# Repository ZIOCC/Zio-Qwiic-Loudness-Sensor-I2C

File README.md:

# Zio Qwiic Loudness Sensor I2C

> This product can be available for purchase [here](https://www.smart-prototyping.com/Zio-Qwiic-Loudness-Sensor-I2C).

Check this [RPI Library](https://github.com/l33tllama/Zio-Loudness-Sensor-Python). 

#### Description

In order to create an environment sensor kit, we should not forget a loudness sensor that can measure the noise level. So, this is a Qwiic version (I2C) of Loudness sensor that can output ADC value (0-1023) to tell you the level of the noise. Also you can use this ADC value into other project, like a sound sensor.

We use an MCU (ATTINY85-20SU) as gateway to turn it into an I2C device. we’ve put the necessary code into it, in case you are interested in this part, check our github channel here. 

The loudness value strongly depends on the distance between the sound source and sensor. For example, if you are playing music with your smartphone, when you place the sensor in close proximity to the phone (within 20cm), with low volume settings, the sensor would output a 500 value, but if you put the sensor 2 meters away, the output value might be 200-300 even when the volume is set to very high. It is similar like the microphone in the KTV. 

This is a [Qwiic compatible](https://www.smart-prototyping.com/Qwiic.html) module, which means you can use [Qwiic cable](https://www.smart-prototyping.com/zio-cables) to quickly connect to other qwiic devices, with no soldering and jumper wire connecting!

#### Specification

* Gateway MCU: ATTINY85-20SU
* I2C address: 0x07- 0x78 (Default:0x38)
* Loudness rate Range: 0-1023
* Dimension: 36.3 x 36.5mm
* Weight: 7.3g

#### Links

* [PCB Source file](https://github.com/ZIOCC/Zio-Qwiic-Loudness-Sensor-I2C)
* [PCB schematic](https://github.com/ZIOCC/Zio-Qwiic-Loudness-Sensor-I2C/blob/master/zio%20qwiic%20loudness%20sensor%20schematic.pdf)
* [Demo code](https://github.com/ZIOCC/Zio-Qwiic-Loudness-Sensor-I2C/tree/master/Codes/Qwiic%20Loudness%20Sensor%20Examples)
* [Gateway firmware](https://github.com/ZIOCC/Zio-Qwiic-Loudness-Sensor-I2C/tree/master/Codes/Qwiic_Loudness_Sensor_Firmware/Qwiic_Loudness_Sensor_Firmware)

> ###### About Zio
> Zio is a new line of open sourced, compact, and grid layout boards, fully integrated for Arduino and Qwiic ecosystem. Designed ideally for wearables, robotics, small-space limitations or other on the go projects. Check out other awesome Zio products [here](https://www.smart-prototyping.com/Zio).

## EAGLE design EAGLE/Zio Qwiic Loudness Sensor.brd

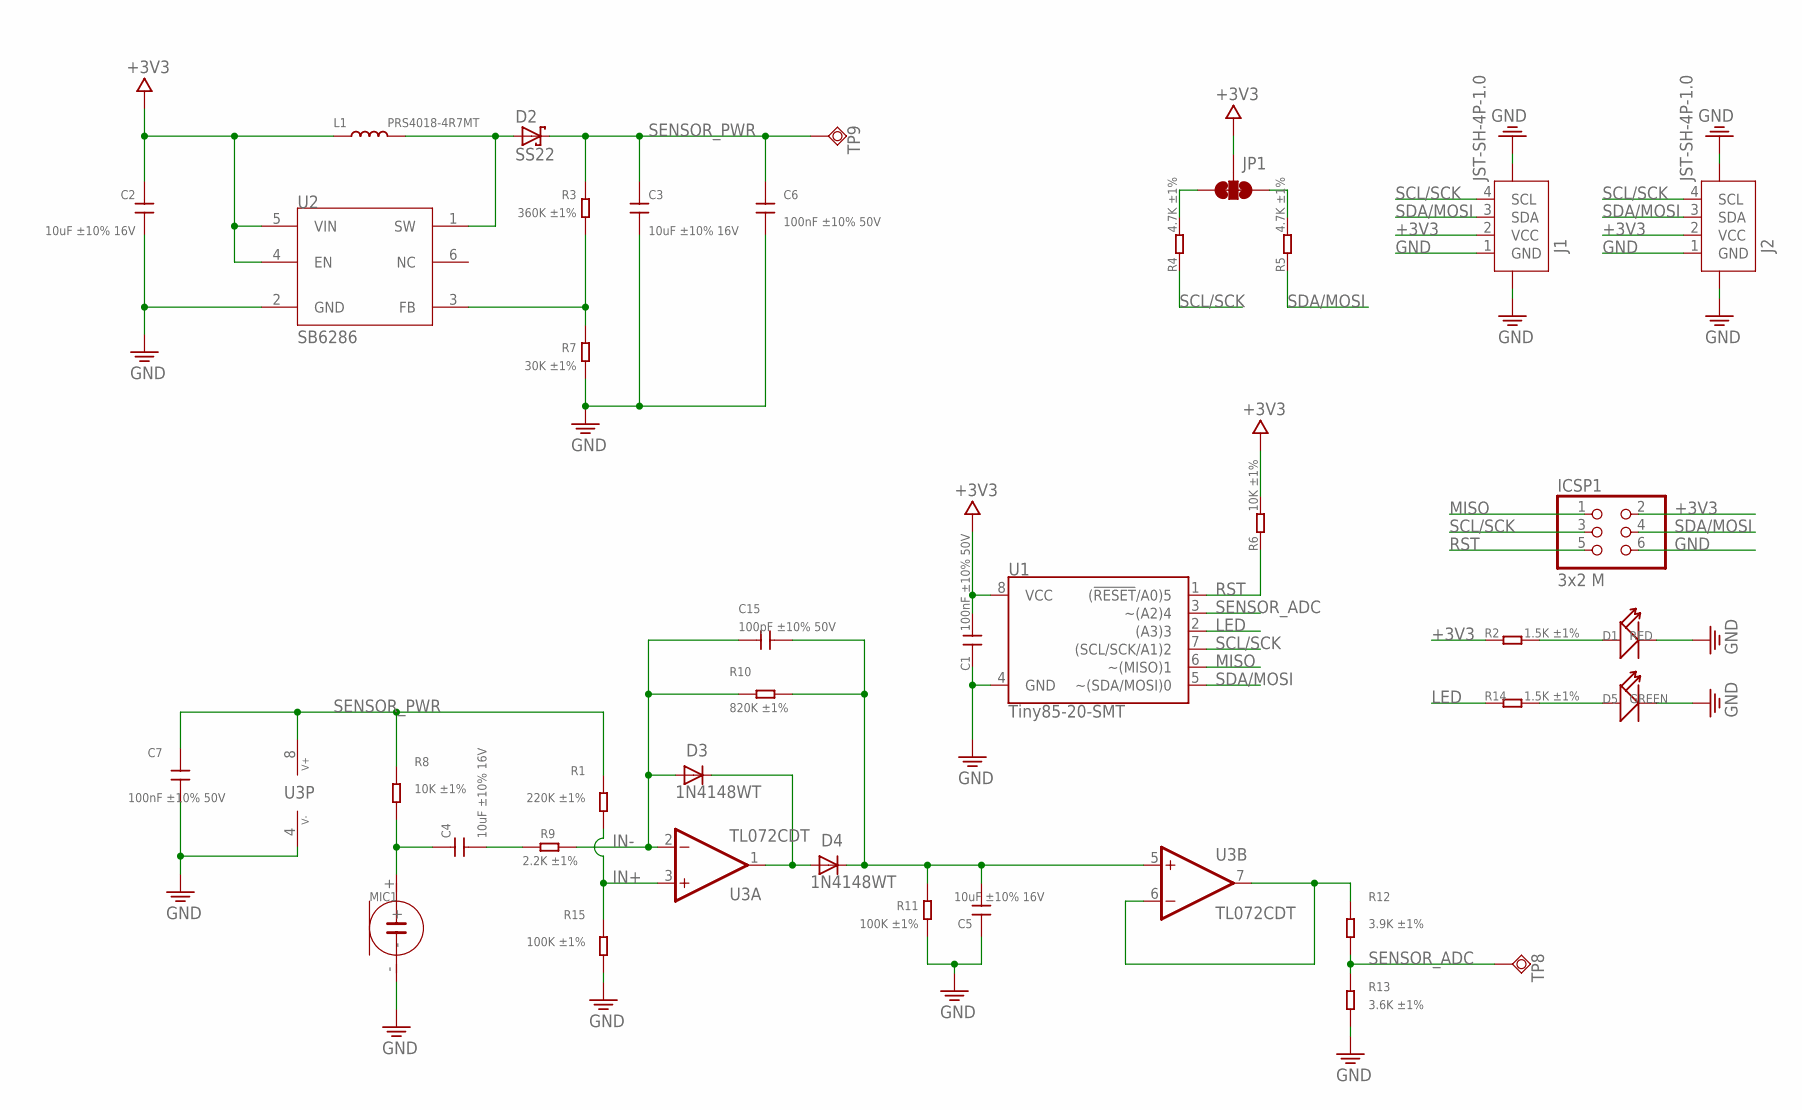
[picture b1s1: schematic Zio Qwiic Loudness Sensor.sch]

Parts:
C1, C6, C7: 100nF ±10% 50V; C0603
C2: 10uF ±10% 16V; C0603
C3, C4, C5: 10uF ±10% 16V; 0603
C15: 100pF ±10% 50V; C0603
D1: RED; LED-0603
D2: SS22; SMA
D3, D4: 1N4148WT; SOD523
D5: GREEN; LED-0603
ICSP1: 3x2 M; 2X03
J1, J2: JST-SH-4P-1.0; JST-SH-4P
JP1: SMT-JUMPER_3_2-NC_TRACE
L1: PRS4018-4R7MT; L4030
MIC1: MIC-2P(EAO-9745-PFA-C1033-28-008); MIC2-D9.7XH4.5MM
R1: 220K ±1%; R0603
R2, R14: 1.5K ±1%; R0603
R3: 360K ±1%; R0603
R4, R5: 4.7K ±1%; R0603
R6, R8: 10K ±1%; R0603
R7: 30K ±1%; R0603
R9: 2.2K ±1%; R0603
R10: 820K ±1%; R0603
R11, R15: 100K ±1%; R0603
R12: 3.9K ±1%; R0603
R13: 3.6K ±1%; R0603
TP8: TPSQTP08R; TP08R
TP9: TPSQTP12R; TP12R
U1: Tiny85-20-SMT; SO08-EIAJ_MCU
U2: SB6286; SOT23-6
U3: TL072CDT; SO08

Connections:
+3V3: C1.2, C2.2, ICSP1.2, J1.2 (VCC), J2.2 (VCC), JP1.2, L1.1, R2.1, R6.2, U1.8 (VCC), U2.4 (EN), U2.5 (VIN)
GND: C1.1, C2.1, C3.1, C5.2, C6.1, C7.1, D1.-, D5.-, ICSP1.6, J1.1 (GND), J1.NC1 (5), J1.NC2 (6), J2.1 (GND), J2.NC1 (5), J2.NC2 (6), MIC1.-, R7.1, R11.1, R13.1, R15.1, U1.4 (GND), U2.2 (GND), U3.4 (V-)
IN+: R1.1, R15.2, U3.3 (+IN)
IN-: C15.2, D3.2 (A), R9.1, R10.1, U3.2 (-IN)
LED: R14.1, U1.2 ((A3)3)
MISO: ICSP1.1, U1.6 (~(MISO)1)
unnamed: D1.+, R2.2
unnamed: R12.2, U3.6 (-IN), U3.7 (OUT)
unnamed: C5.1, C15.1, D4.1 (K), R10.2, R11.2, U3.5 (+IN)
unnamed: R3.1, R7.2, U2.3 (FB)
unnamed: D5.+, R14.2
unnamed: JP1.3, R4.2
unnamed: D3.1 (K), D4.2 (A), U3.1 (OUT)
unnamed: JP1.1, R5.2
unnamed: C4.2, MIC1.+, R8.1
unnamed: C4.1, R9.2
RST: ICSP1.5, R6.1, U1.1 ((!RESET!/A0)5)
SCL/SCK: ICSP1.3, J1.4 (SCL), J2.4 (SCL), R4.1, U1.7 ((SCL/SCK/A1)2)
SDA/MOSI: ICSP1.4, J1.3 (SDA), J2.3 (SDA), R5.1, U1.5 (~(SDA/MOSI)0)
SENSOR_ADC: R12.1, R13.2, TP8.TP, U1.3 (~(A2)4)
SENSOR_PWR: C3.2, C6.2, C7.2, D2.P$1 (C), R1.2, R3.2, R8.2, TP9.TP, U3.8 (V+)
SW: D2.P$2 (A), L1.2, U2.1 (SW)

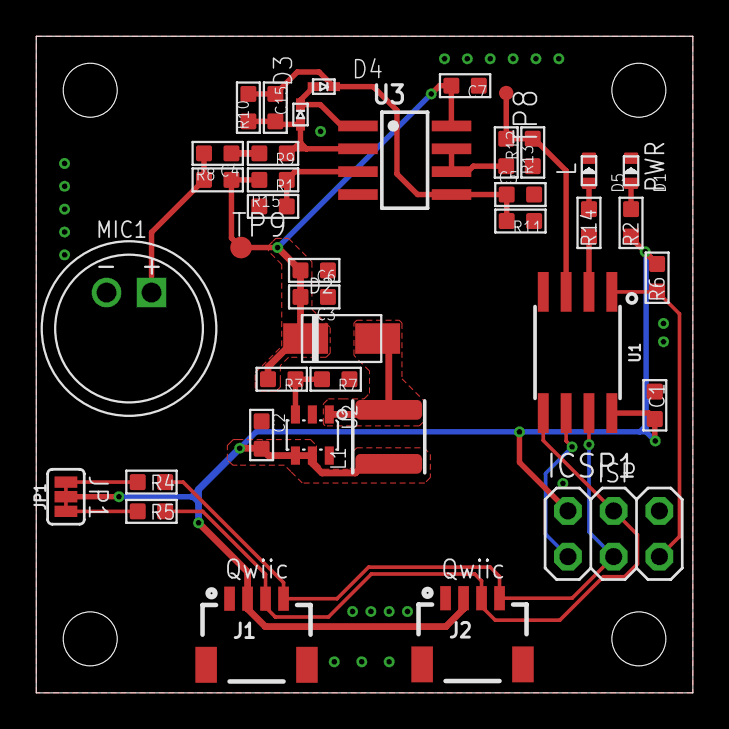
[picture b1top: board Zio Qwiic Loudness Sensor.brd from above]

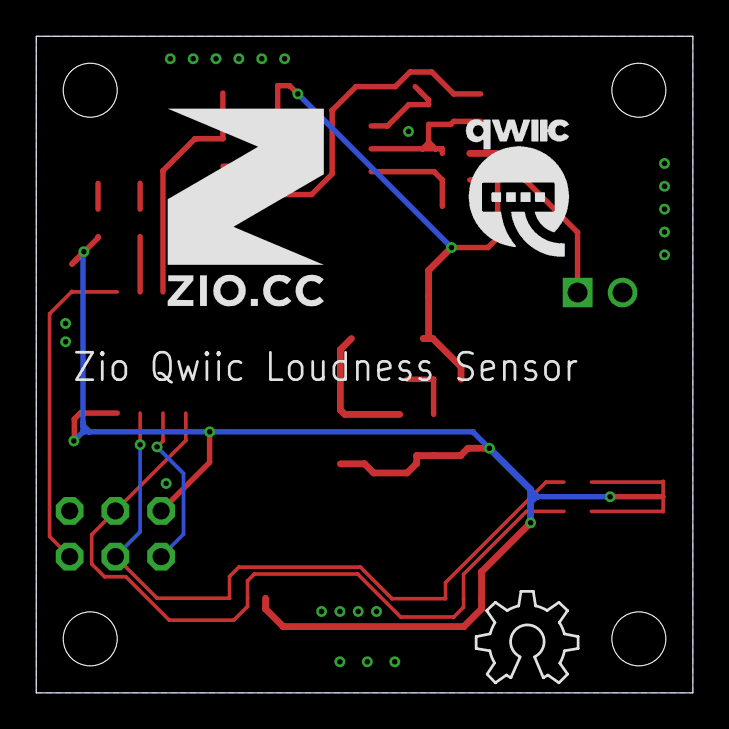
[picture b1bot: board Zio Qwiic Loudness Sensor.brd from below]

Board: 2 copper layers, 36.5 x 36.5 mm, 42 parts (3 on the bottom side), 22 nets.

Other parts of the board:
U$3: 11MM
U$4: QWIIC-LOGO-LARGE
U$5: OSHW_6X200_NOTEXT

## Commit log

2019-02-21 Update Loudness_Sensor_OLED.ino
    Make changes to the initialization of OLED display matched to the updated Adafruit library
